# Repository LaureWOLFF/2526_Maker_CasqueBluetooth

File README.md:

# 🎧 2526_Maker_CasqueBluetooth: Création d'un casque bluetooth DIY

## 📌 Présentation du Projet

Le but de ce projet est de créer un casque bluetooth en mobilisant les compétences apprises lors de l'option **Maker** de deuxième année de l'**ENSEA**. Pour réaliser ce casque, le choix du microcontroleur c'est porté sur l'utilisation d'un **ESP32-S3-MINI-1-N8**. La structure mécanique a été entièrement modélisée sur **Onshape** avec une attention particulière portée à l'intégration électronique et à la durabilité tandis que la conception électronique a été réalisée sur Kicad.

### Caractéristiques Principales
* **Micronctroleur :** ESP32-S3-MINI-N8.
* **Diamètre des oreillettes :** 82 mm.
* **Interface :** Contrôle du volume et lecture via 3 boutons physiques (GPIO 0, 1, 2).
* **Connectivité :** USB-C 16 pins.
* **Architecture Audio :** Flux numérique I2S (Pins 6, 7, 8) vers DAC/Ampli.

---

## 🛠 Technologies & Outils
* **Mécanique :** Onshape (Modélisation 3D).
* **Électronique :** KiCad (Conception du PCB).
* **Développement :** Arduino IDE 1.8.19.

## 📋 État du Prototype
* **Hardware :** PCB soudé et fonctionnel (LED verte OK).
* **Mécanique :** Impression 3D terminée et finalisée.
* **Firmware :** En cours d'optimisation pour la reconnaissance USB Audio.

---

## ⚡L'impasse du Bluetooth classique sur l'ESP32-S3

Lors de la progammation du PCB, un problème est intervenu. Il est impossible de compiler le code car l'ESP32-S2-MINI-N8. En effet conttairement au téléphone qui a un protocole bluetooth pour l'audio de A2DP (Classic), l'ESP32 ne finctionne que en Bluetooth LE. Cette erreur dans le choix du composant a empecher de réliser  la finialisation de ce pojet. Car la bibliothèque de référence `ESP32-A2DP` est= incompatible avec cette puce. Le S3 est conçu pour le **Bluetooth LE (Low Energy)** et le futur standard **LE Audio**, qui nécessite un smartphone très récent.

    1. Modification du PCB
Pour palierà ce problème, une possibilité eest d'ajoutéé un module Bluetooth Audio dédié gérant le profil A2DP. Ainsi ainsi l'ESP32 serait utilisé pour traiter l'information (la munique) et le module pour la transmmetre. Cependant, le PCB devait être modifier et avec le délai serré, il était impossible de commander un nouveau PCB modifié.

    2. La solution Wi-Fi
Il existe une possibilitée d'utiliser le Wi-Fi pour le streaming (Spotify Connect). Cependant, le casque devenait dépendant d'un réseau Wi-Fi local, perdant son utilité en déplacement.

      3. La Solution USB DAC
Pour sauver le projet sans changer le PCB déjà soudé, une autre solution est envisageable vers un mode **USB DAC**. 
En utilisant les pins natives **D- (GPIO 19)** et **D+ (GPIO 20)** de l'ESP32-S3, le casque est reconnu comme une carte son externe par le téléphone. Ainsi, il y a la possibilité de transformer le prototype d'un casque bluetooth à un casque filiaire.

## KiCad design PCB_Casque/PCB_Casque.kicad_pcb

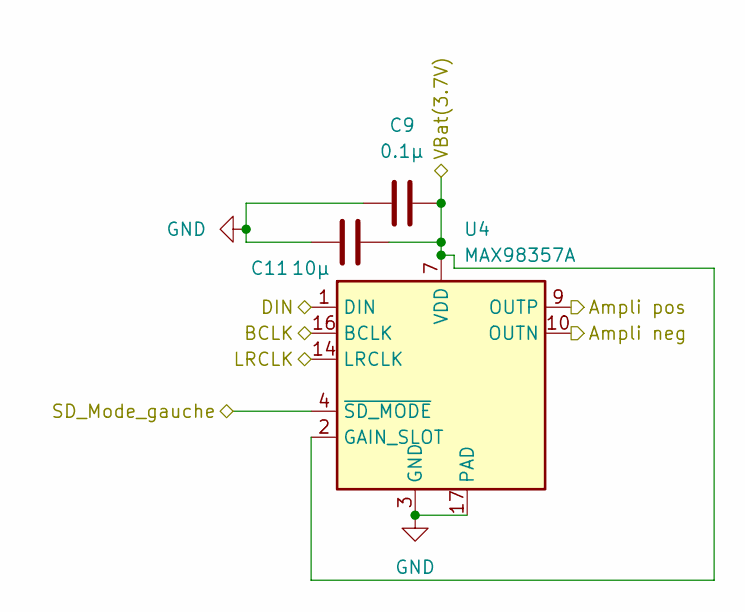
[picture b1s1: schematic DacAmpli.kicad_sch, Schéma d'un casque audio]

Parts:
C9: 0.1µ; C_0402_1005Metric_Pad0.74x0.62mm_HandSolder
C11: 10µ; C_0603_1608Metric_Pad1.08x0.95mm_HandSolder
U4: MAX98357A; TQFN-16-1EP_3x3mm_P0.5mm_EP1.23x1.23mm

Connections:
/Abaisseur/Vbat(3.7V): C9.1, C11.1, U4.2 (GAIN_SLOT), U4.7 (VDD), U4.8 (VDD); also elsewhere on the board
/DAC ampli droit/BCLK: U4.16 (BCLK); also elsewhere on the board
/DAC ampli droit/DIN: U4.1 (DIN); also elsewhere on the board
/DAC ampli droit/LRCLK: U4.14 (LRCLK); also elsewhere on the board
/DAC ampli droit/SD_Mode_droit: U4.4 (~SD_MODE); also elsewhere on the board
/DAC ampli gauche/Ampli neg: U4.10 (OUTN); also elsewhere on the board
/DAC ampli gauche/Ampli pos: U4.9 (OUTP); also elsewhere on the board
GND: C9.2, C11.2, U4.3 (GND), U4.11 (GND), U4.15 (GND), U4.17 (PAD); also elsewhere on the board

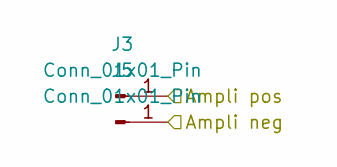
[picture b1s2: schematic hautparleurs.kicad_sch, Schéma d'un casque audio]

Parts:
J3, J5: Conn_01x01_Pin; TestPoint_Pad_D2.0mm

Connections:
/DAC ampli gauche/Ampli neg: J5.1; also elsewhere on the board
/DAC ampli gauche/Ampli pos: J3.1; also elsewhere on the board

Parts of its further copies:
J4, J6: Conn_01x01_Pin; TestPoint_Pad_D2.0mm

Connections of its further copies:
/DAC ampli droit/Ampli neg: J6.1; also elsewhere on the board
/DAC ampli droit/Ampli pos: J4.1; also elsewhere on the board

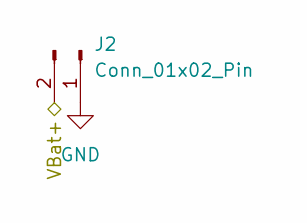
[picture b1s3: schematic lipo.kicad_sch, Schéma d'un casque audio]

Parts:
J2: Conn_01x02_Pin; JST_PH_B2B-PH-K_1x02_P2.00mm_Vertical

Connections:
/Abaisseur/Vbat(3.7V): J2.2; also elsewhere on the board
GND: J2.1; also elsewhere on the board

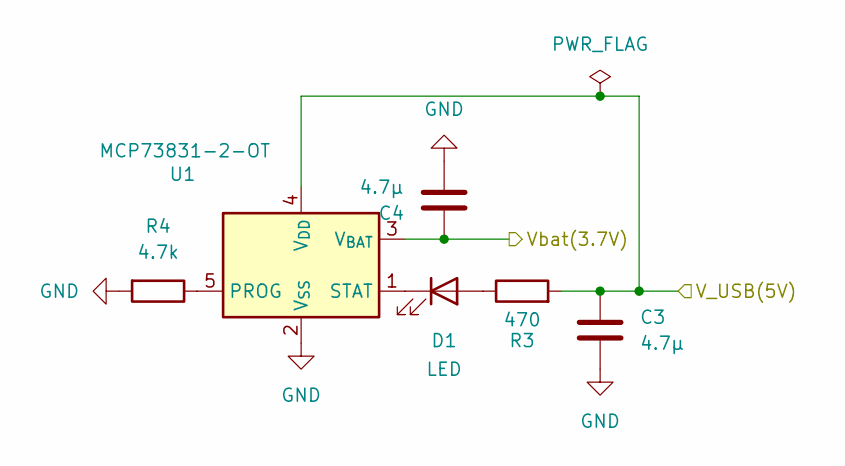
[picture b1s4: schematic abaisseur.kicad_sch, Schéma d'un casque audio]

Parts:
C3, C4: 4.7µ; C_0402_1005Metric_Pad0.74x0.62mm_HandSolder
D1: LED; LED_0603_1608Metric_Pad1.05x0.95mm_HandSolder
R3: 470; R_0402_1005Metric_Pad0.72x0.64mm_HandSolder
R4: 4.7k; R_0402_1005Metric_Pad0.72x0.64mm_HandSolder
U1: MCP73831-2-OT; SOT-23-5

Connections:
/Abaisseur/V_USB(5V): C3.1, R3.2, U1.4 (V_{DD}); also elsewhere on the board
/Abaisseur/Vbat(3.7V): C4.1, U1.3 (V_{BAT}); also elsewhere on the board
GND: C3.2, C4.2, R4.2, U1.2 (V_{SS}); also elsewhere on the board
unnamed: D1.2 (A), R3.1
unnamed: D1.1 (K), U1.1 (STAT)
unnamed: R4.1, U1.5 (PROG)

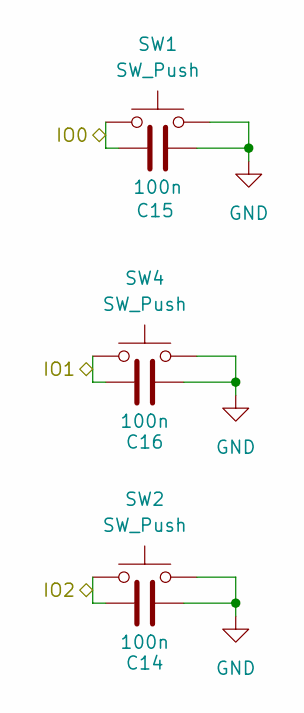
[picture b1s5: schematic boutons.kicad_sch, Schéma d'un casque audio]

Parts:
C14, C15, C16: 100n; C_0402_1005Metric_Pad0.74x0.62mm_HandSolder
SW1, SW2, SW4: SW_Push; SW_Tactile_SPST_Angled_PTS645Vx58-2LFS

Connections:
/ESP23_s3_mini_1_N8/IO0: C15.2, SW1.1; also elsewhere on the board
/ESP23_s3_mini_1_N8/IO1: C16.2, SW4.1; also elsewhere on the board
/ESP23_s3_mini_1_N8/IO2: C14.2, SW2.1; also elsewhere on the board
GND: C14.1, C15.1, C16.1, SW1.2, SW2.2, SW4.2; also elsewhere on the board

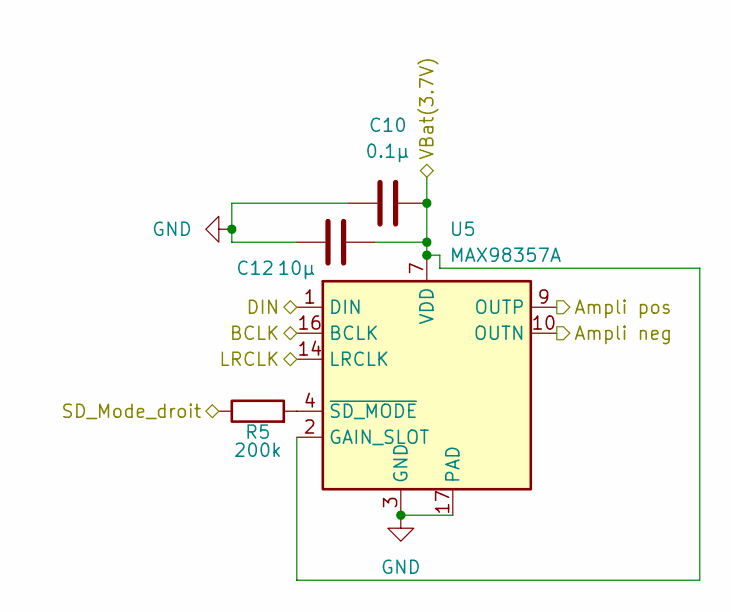
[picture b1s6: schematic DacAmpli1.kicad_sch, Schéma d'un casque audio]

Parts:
C10: 0.1µ; C_0402_1005Metric_Pad0.74x0.62mm_HandSolder
C12: 10µ; C_0603_1608Metric_Pad1.08x0.95mm_HandSolder
R5: 200k; R_0402_1005Metric_Pad0.72x0.64mm_HandSolder
U5: MAX98357A; TQFN-16-1EP_3x3mm_P0.5mm_EP1.23x1.23mm

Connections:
/Abaisseur/Vbat(3.7V): C10.1, C12.1, U5.2 (GAIN_SLOT), U5.7 (VDD), U5.8 (VDD); also elsewhere on the board
/DAC ampli droit/Ampli neg: U5.10 (OUTN); also elsewhere on the board
/DAC ampli droit/Ampli pos: U5.9 (OUTP); also elsewhere on the board
/DAC ampli droit/BCLK: U5.16 (BCLK); also elsewhere on the board
/DAC ampli droit/DIN: U5.1 (DIN); also elsewhere on the board
/DAC ampli droit/LRCLK: U5.14 (LRCLK); also elsewhere on the board
/DAC ampli droit/SD_Mode_droit: R5.1; also elsewhere on the board
GND: C10.2, C12.2, U5.3 (GND), U5.11 (GND), U5.15 (GND), U5.17 (PAD); also elsewhere on the board
unnamed: R5.2, U5.4 (~SD_MODE)

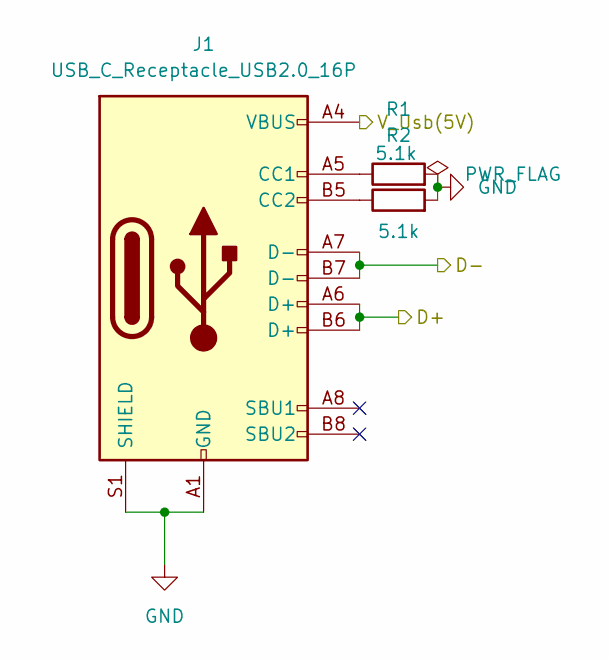
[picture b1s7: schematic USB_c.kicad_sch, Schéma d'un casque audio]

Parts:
J1: USB_C_Receptacle_USB2.0_16P; USB_C_Receptacle_GCT_USB4105-xx-A_16P_TopMnt_Horizontal
R1, R2: 5.1k; R_0402_1005Metric_Pad0.72x0.64mm_HandSolder

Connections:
/Abaisseur/V_USB(5V): J1.A4 (VBUS), J1.A9 (VBUS), J1.B4 (VBUS), J1.B9 (VBUS); also elsewhere on the board
/ESP23_s3_mini_1_N8/D+: J1.A6 (D+), J1.B6 (D+); also elsewhere on the board
/ESP23_s3_mini_1_N8/D-: J1.A7 (D-), J1.B7 (D-); also elsewhere on the board
GND: J1.A1 (GND), J1.A12 (GND), J1.B1 (GND), J1.B12 (GND), J1.S1 (SHIELD), R1.2, R2.2; also elsewhere on the board
unnamed: J1.A5 (CC1), R1.1
unnamed: J1.B5 (CC2), R2.1

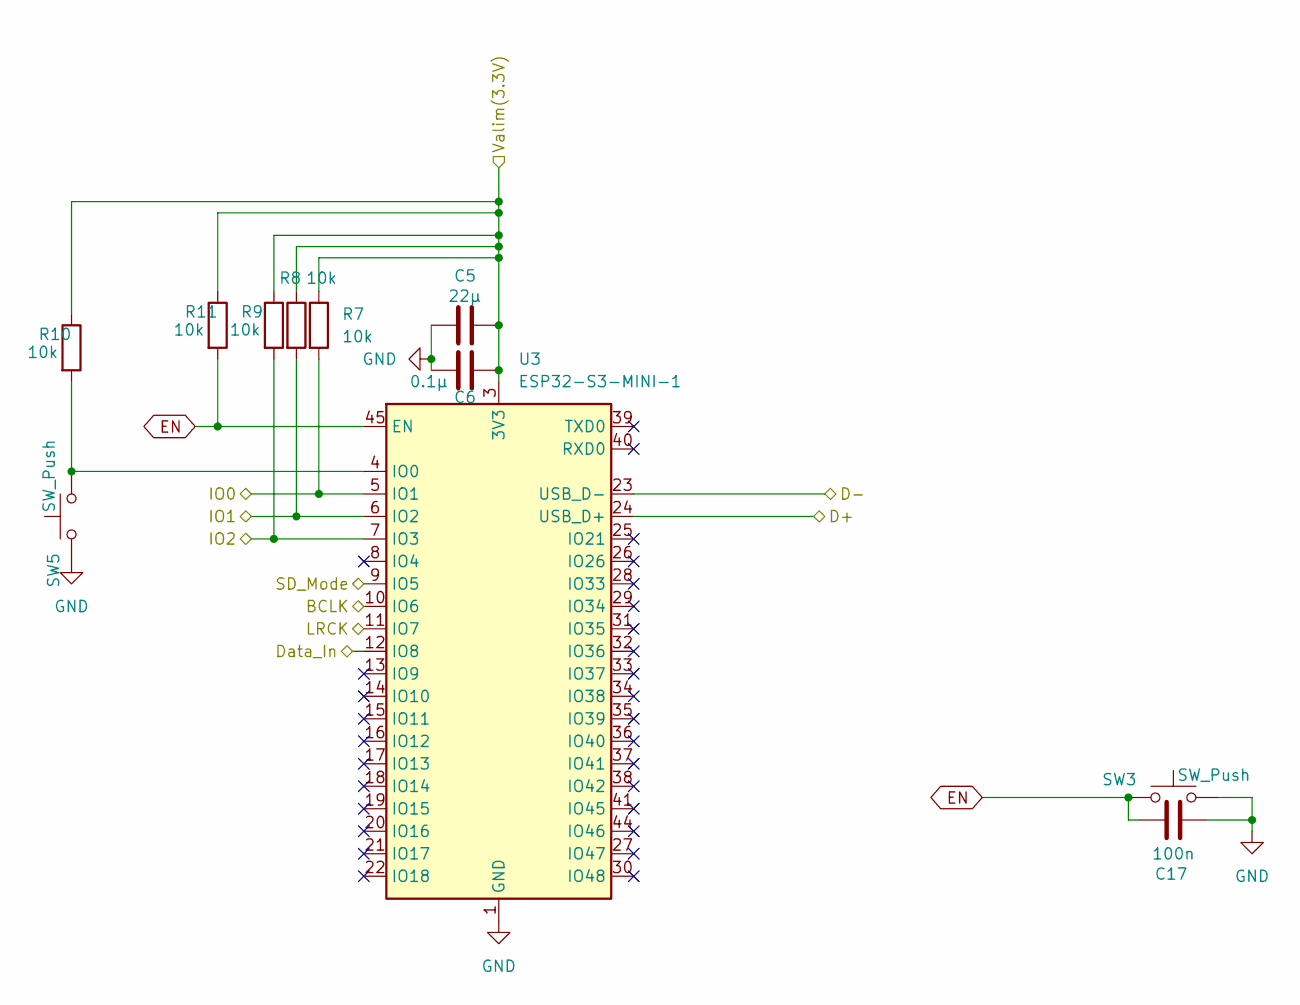
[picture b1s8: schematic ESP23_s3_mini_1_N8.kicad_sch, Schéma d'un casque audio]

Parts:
C5: 22µ; C_0603_1608Metric_Pad1.08x0.95mm_HandSolder
C6: 0.1µ; C_0402_1005Metric_Pad0.74x0.62mm_HandSolder
C17: 100n; C_0402_1005Metric_Pad0.74x0.62mm_HandSolder
R7, R8, R9, R10, R11: 10k; R_0402_1005Metric_Pad0.72x0.64mm_HandSolder
SW3, SW5: SW_Push; 435171014816
U3: ESP32-S3-MINI-1; ESP32-S2-MINI-1

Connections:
/DAC ampli droit/BCLK: U3.10 (IO6); also elsewhere on the board
/DAC ampli droit/DIN: U3.12 (IO8); also elsewhere on the board
/DAC ampli droit/LRCLK: U3.11 (IO7); also elsewhere on the board
/DAC ampli droit/SD_Mode_droit: U3.9 (IO5); also elsewhere on the board
/ESP23_s3_mini_1_N8/D+: U3.24 (USB_D+); also elsewhere on the board
/ESP23_s3_mini_1_N8/D-: U3.23 (USB_D-); also elsewhere on the board
/ESP23_s3_mini_1_N8/IO0: R7.2, U3.5 (IO1); also elsewhere on the board
/ESP23_s3_mini_1_N8/IO1: R8.2, U3.6 (IO2); also elsewhere on the board
/ESP23_s3_mini_1_N8/IO2: R9.2, U3.7 (IO3); also elsewhere on the board
/ESP23_s3_mini_1_N8/Valim(3.3V): C5.1, C6.2, R7.1, R8.1, R9.1, R10.1, R11.1, U3.3 (3V3); also elsewhere on the board
EN: C17.2, R11.2, SW3.1, U3.45 (EN)
GND: C5.2, C6.1, C17.1, SW3.2, SW5.1, U3.1 (GND), U3.2 (GND), U3.42 (GND), U3.43 (GND), U3.46 (GND), U3.47 (GND), U3.48 (GND), U3.49 (GND), U3.50 (GND), U3.51 (GND), U3.52 (GND), U3.53 (GND), U3.54 (GND), U3.55 (GND), U3.56 (GND), U3.57 (GND), U3.58 (GND), U3.59 (GND), U3.60 (GND), U3.61 (GND), U3.62 (GND), U3.63 (GND), U3.64 (GND), U3.65 (GND); also elsewhere on the board
unnamed: R10.2, SW5.2, U3.4 (IO0)

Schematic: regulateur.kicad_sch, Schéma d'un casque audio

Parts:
C1, C2: 1µ; C_0402_1005Metric_Pad0.74x0.62mm_HandSolder
U2: AP2112K-3.3; SOT-23-5

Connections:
/Abaisseur/Vbat(3.7V): C1.1, U2.1 (VIN), U2.3 (EN); also elsewhere on the board
/ESP23_s3_mini_1_N8/Valim(3.3V): C2.1, U2.5 (VOUT); also elsewhere on the board
GND: C1.2, C2.2, U2.2 (GND); also elsewhere on the board

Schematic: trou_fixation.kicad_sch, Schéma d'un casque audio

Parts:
H1, H2, H3, H4: MountingHole; MountingHole_2.7mm_M2.5

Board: 2 copper layers, 41 parts (0 on the bottom side), 25 nets, no tracks yet.

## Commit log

2026-01-21 Ajout du diagramme gantt 21/01
2026-01-21 Ajout des pièces CAO 21/01
2026-01-26 sans le CAD hors projet
2026-03-19 Prototypage du PCB
2026-03-23 ajout du PCB version final + elt du design
2026-04-16 Ajout du code
2026-05-03 Video de 1min20
2026-05-05 Ajout des TDs
2026-05-05 Ajout de la batterie
